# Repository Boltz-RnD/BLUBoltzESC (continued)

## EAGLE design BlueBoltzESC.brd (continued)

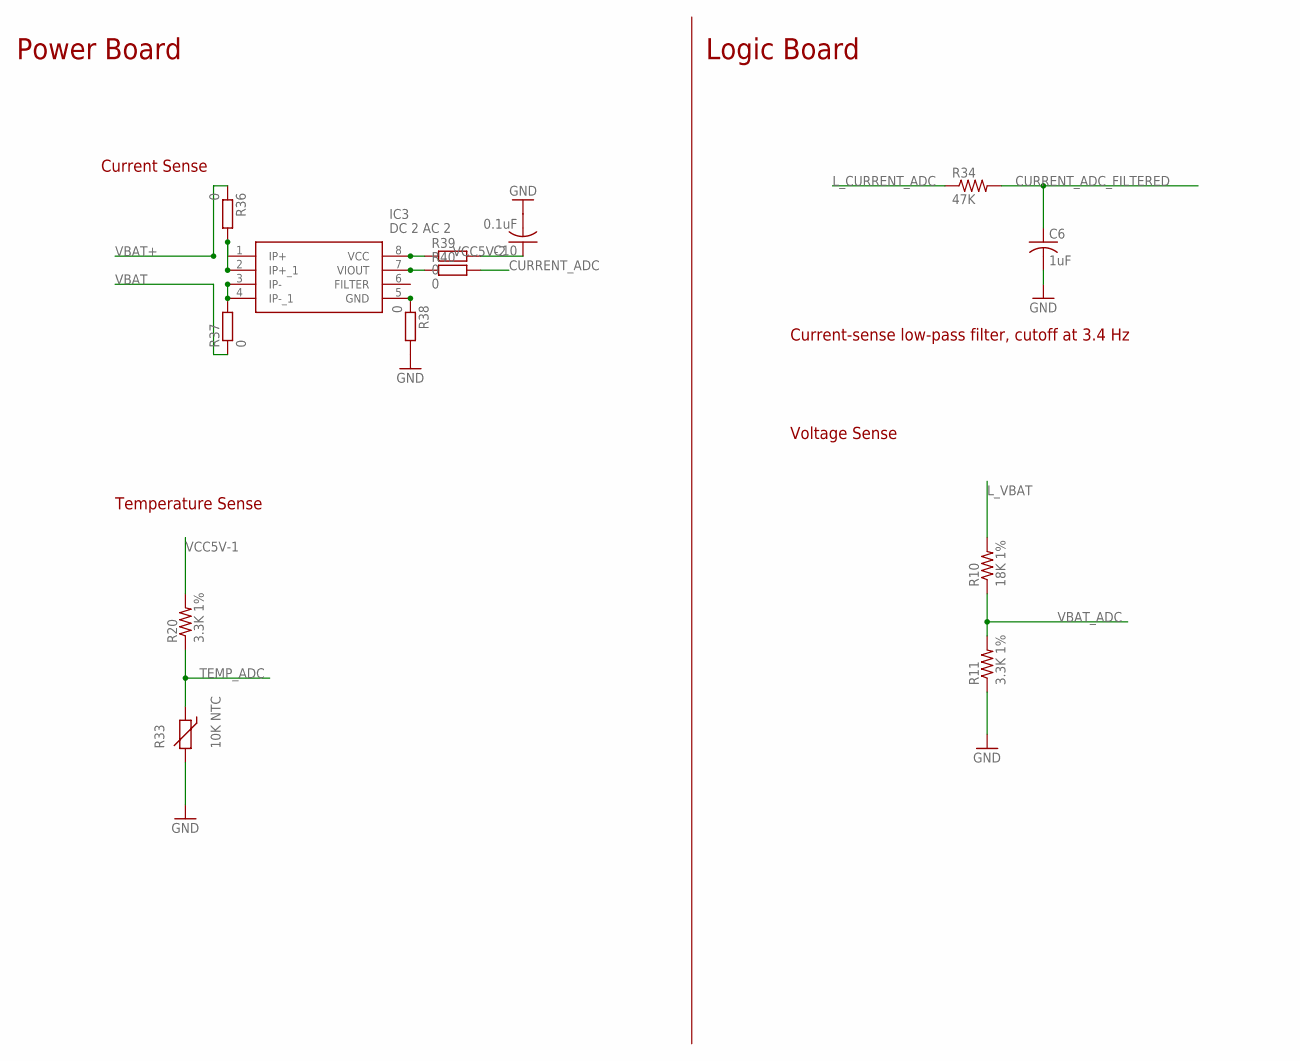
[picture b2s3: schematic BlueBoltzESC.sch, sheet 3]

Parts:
C6: 1uF; C025-030X050
C10: 0.1uF; C025-030X050
IC3: DC 2 AC 2; SOIC127P600X175-8N
R10: 18K 1%; 0207/10
R11, R20: 3.3K 1%; 0207/10
R33: 10K NTC; R-5
R34: 47K; 0207/10
R36, R37, R38, R39, R40: 0; MINI_MELF-0102R

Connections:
CURRENT_ADC: R40.2; also elsewhere on the board
CURRENT_ADC_FILTERED: C6.1, R34.2; also elsewhere on the board
GND: C10.2, R33.2, R38.2; also elsewhere on the board
L_CURRENT_ADC: R34.1; also elsewhere on the board
L_GND: C6.2, R11.1; also elsewhere on the board
L_VBAT: R10.2; also elsewhere on the board
unnamed: IC3.1 (IP+), IC3.2 (IP+_1), R36.2
unnamed: IC3.3 (IP-), IC3.4 (IP-_1), R37.2
unnamed: IC3.5 (GND), R38.1
unnamed: IC3.8 (VCC), R39.1
unnamed: IC3.7 (VIOUT), R40.1
TEMP_ADC: R20.1, R33.1; also elsewhere on the board
VBAT: R37.1; also elsewhere on the board
VBAT+: R36.1; also elsewhere on the board
VBAT_ADC: R10.1, R11.2; also elsewhere on the board
VCC5V-1: R20.2; also elsewhere on the board
VCC5V-2: C10.1, R39.2; also elsewhere on the board

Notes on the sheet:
Power Board
Logic Board
Current-sense low-pass filter, cutoff at 3.4 Hz
Voltage Sense
Current Sense
Temperature Sense

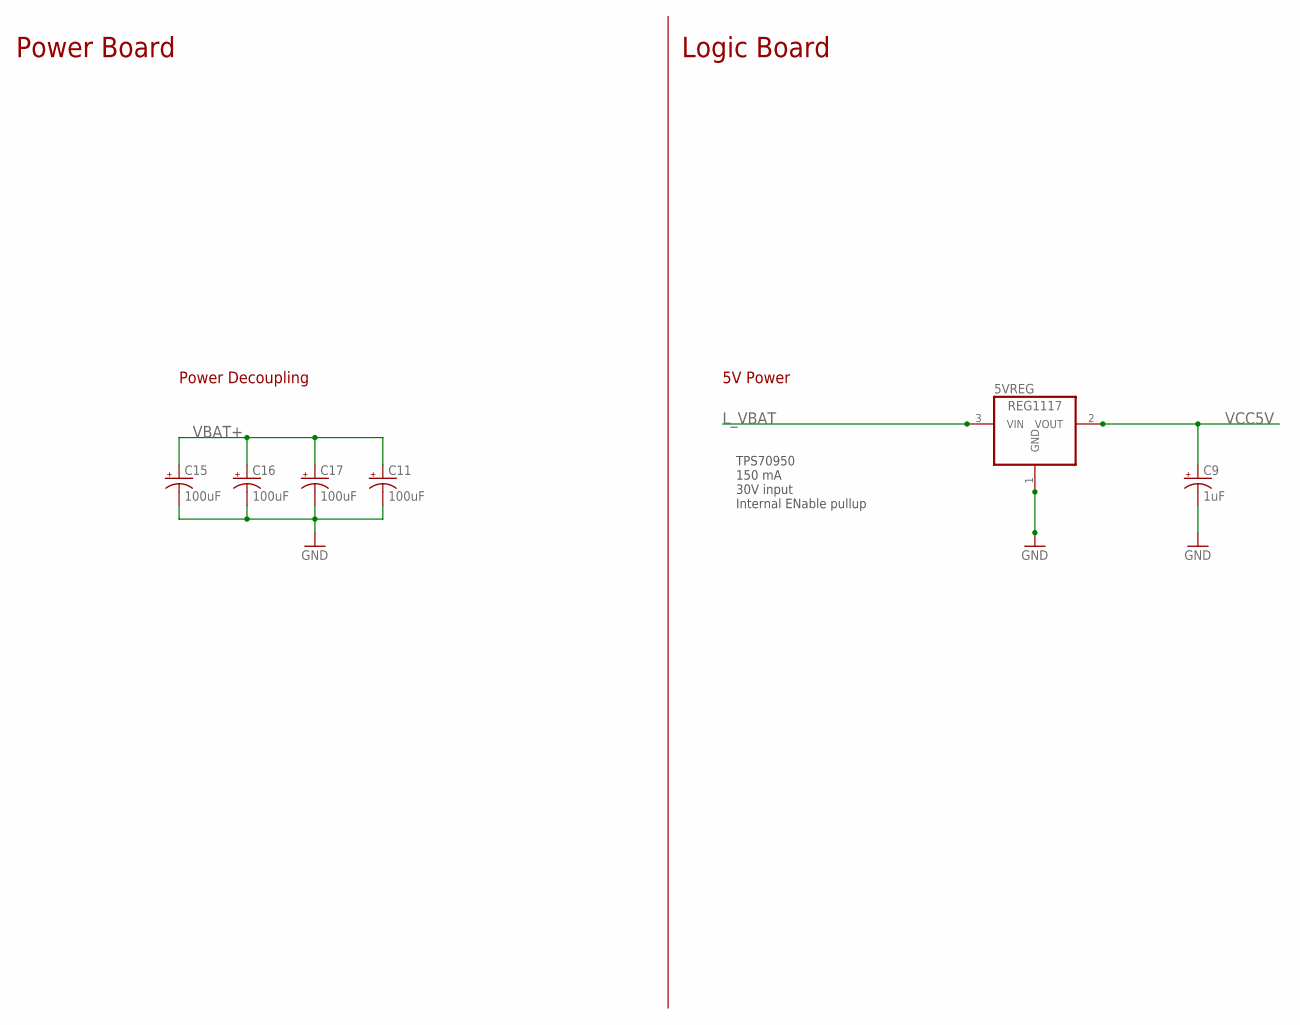
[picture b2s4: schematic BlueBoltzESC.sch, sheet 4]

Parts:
5VREG: REG1117; SOT223
C9: 1uF; E2,5-7
C11, C15, C16, C17: 100uF; E3,5-8

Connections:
GND: C11.-, C15.-, C16.-, C17.-; also elsewhere on the board
L_GND: 5VREG.1 (GND), C9.-; also elsewhere on the board
L_VBAT: 5VREG.3 (VIN); also elsewhere on the board
VBAT+: C11.+, C15.+, C16.+, C17.+; also elsewhere on the board
VCC5V: 5VREG.2 (VOUT), C9.+; also elsewhere on the board

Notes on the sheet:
Power Board
Logic Board
Power Decoupling
5V Power
TPS70950 150 mA 30V input Internal ENable pullup

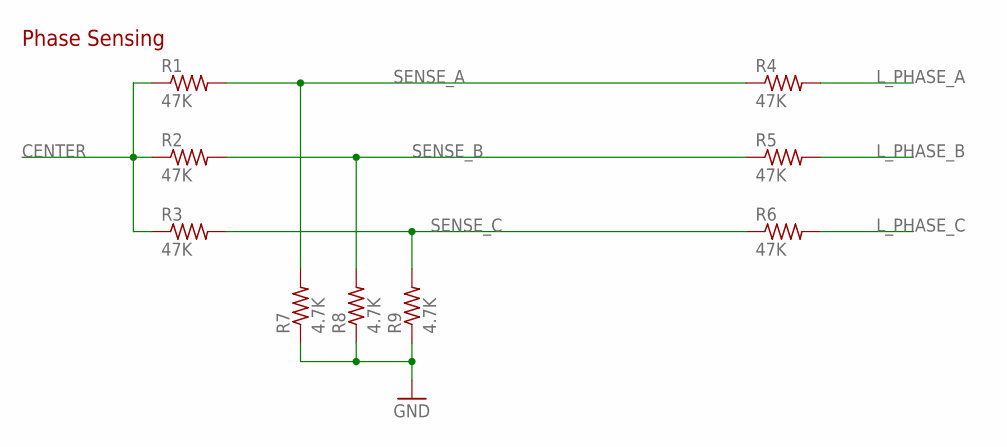
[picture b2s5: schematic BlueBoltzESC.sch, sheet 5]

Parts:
R1, R2, R3, R4, R5, R6: 47K; 0207/10
R7, R8, R9: 4.7K; 0207/10

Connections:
CENTER: R1.1, R2.1, R3.1; also elsewhere on the board
L_GND: R7.1, R8.1, R9.1; also elsewhere on the board
L_PHASE_A: R4.2; also elsewhere on the board
L_PHASE_B: R5.2; also elsewhere on the board
L_PHASE_C: R6.2; also elsewhere on the board
SENSE_A: R1.2, R4.1, R7.2; also elsewhere on the board
SENSE_B: R2.2, R5.1, R8.2; also elsewhere on the board
SENSE_C: R3.2, R6.1, R9.2; also elsewhere on the board

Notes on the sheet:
Phase Sensing

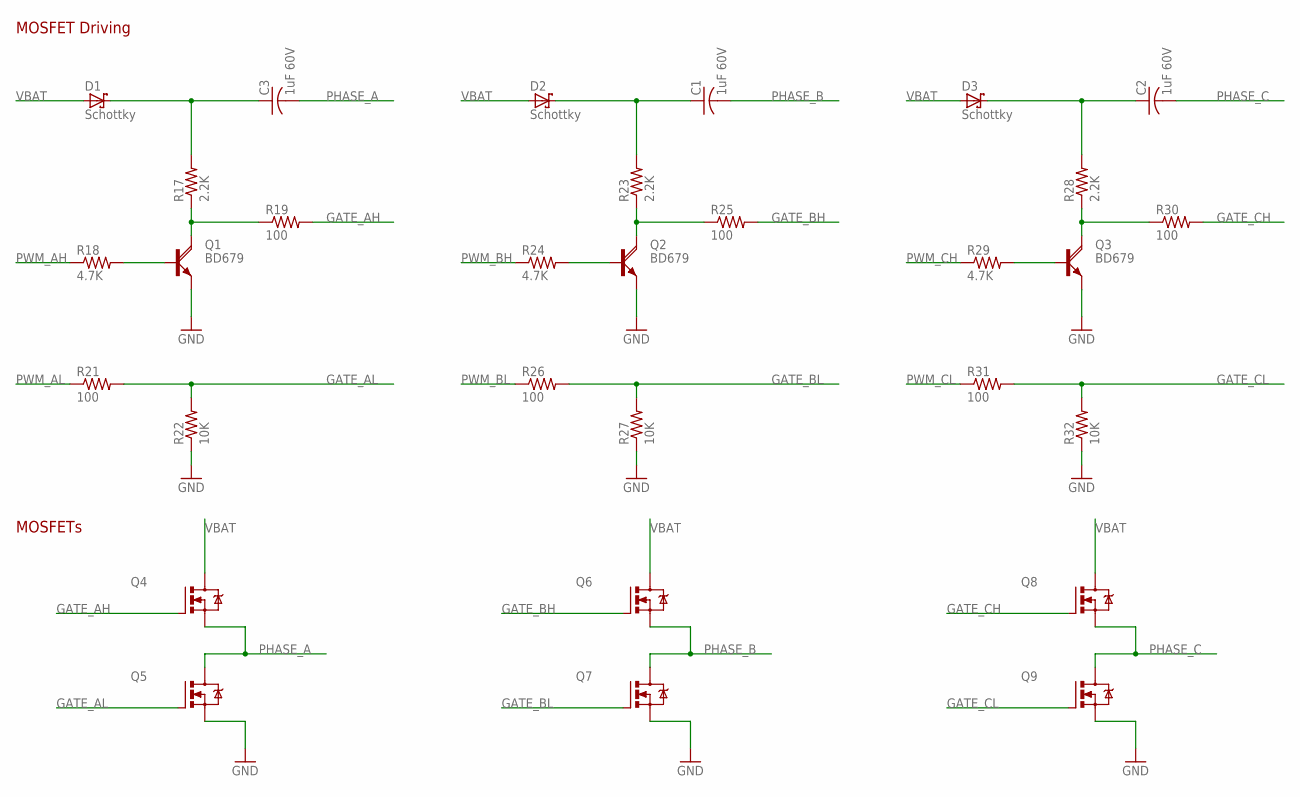
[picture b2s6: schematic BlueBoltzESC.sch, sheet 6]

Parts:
C1, C2, C3: 1uF 60V; C025-040X050
D1, D2, D3: Schottky; DO35-7
Q1, Q2, Q3: BD679; TO126AV
Q4, Q5, Q6, Q7, Q8, Q9: IRLZ44Z; TO220BH
R17, R23, R28: 2.2K; 0207/10
R18, R24, R29: 4.7K; 0207/10
R19, R21, R25, R26, R30, R31: 100; M3216
R22, R27, R32: 10K; M3216

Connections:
GATE_AH: Q4.G, R19.2
GATE_AL: Q5.G, R21.2, R22.2
GATE_BH: Q6.G, R25.2
GATE_BL: Q7.G, R26.2, R27.2
GATE_CH: Q8.G, R30.2
GATE_CL: Q9.G, R31.2, R32.2
GND: Q1.E, Q2.E, Q3.E, Q5.S, Q7.S, Q9.S, R22.1, R27.1, R32.1; also elsewhere on the board
unnamed: Q1.B, R18.2
unnamed: Q1.C, R17.1, R19.1
unnamed: Q2.B, R24.2
unnamed: Q2.C, R23.1, R25.1
unnamed: Q3.B, R29.2
unnamed: Q3.C, R28.1, R30.1
unnamed: C3.1, D1.C, R17.2
unnamed: C1.1, D2.C, R23.2
unnamed: C2.1, D3.C, R28.2
PHASE_A: C3.2, Q4.S, Q5.D; also elsewhere on the board
PHASE_B: C1.2, Q6.S, Q7.D; also elsewhere on the board
PHASE_C: C2.2, Q8.S, Q9.D; also elsewhere on the board
PWM_AH: R18.1; also elsewhere on the board
PWM_AL: R21.1; also elsewhere on the board
PWM_BH: R24.1; also elsewhere on the board
PWM_BL: R26.1; also elsewhere on the board
PWM_CH: R29.1; also elsewhere on the board
PWM_CL: R31.1; also elsewhere on the board
VBAT: D1.A, D2.A, D3.A, Q4.D, Q6.D, Q8.D; also elsewhere on the board

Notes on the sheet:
MOSFETs
MOSFET Driving

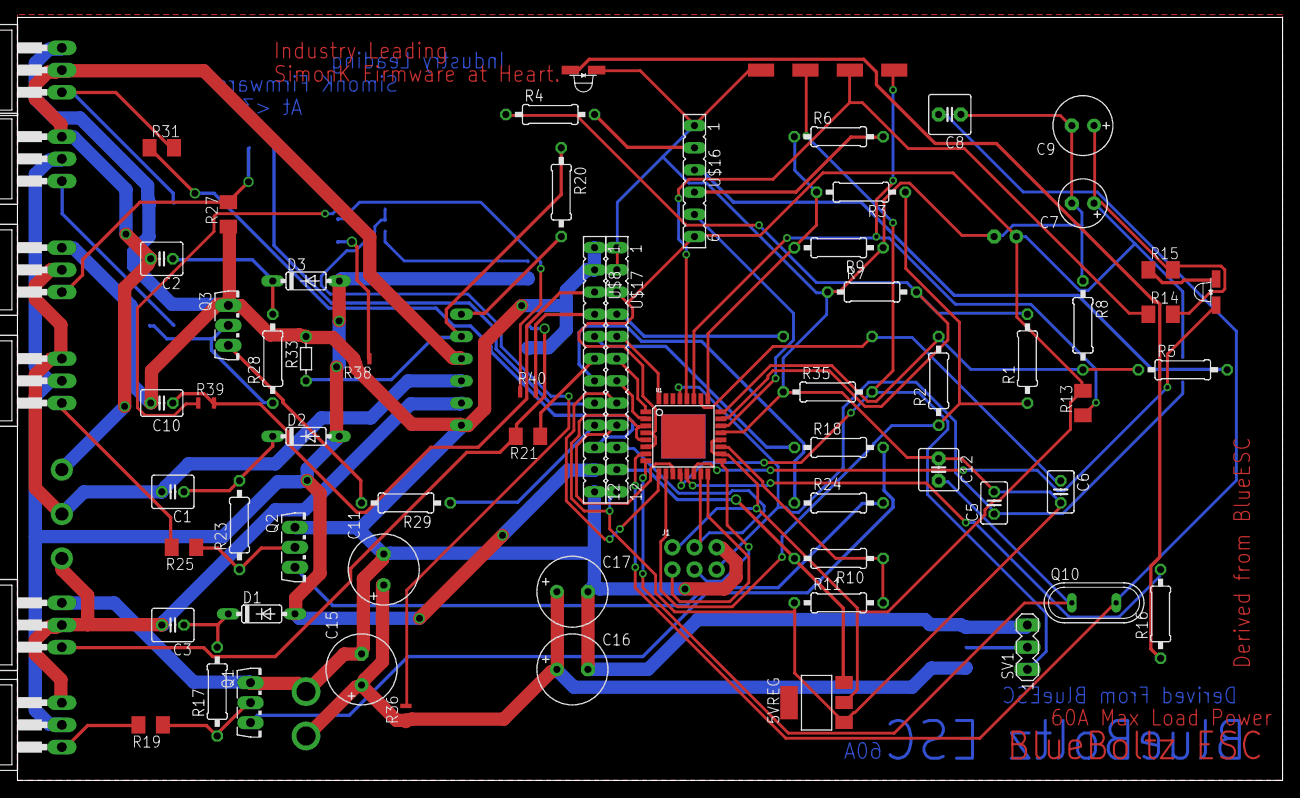
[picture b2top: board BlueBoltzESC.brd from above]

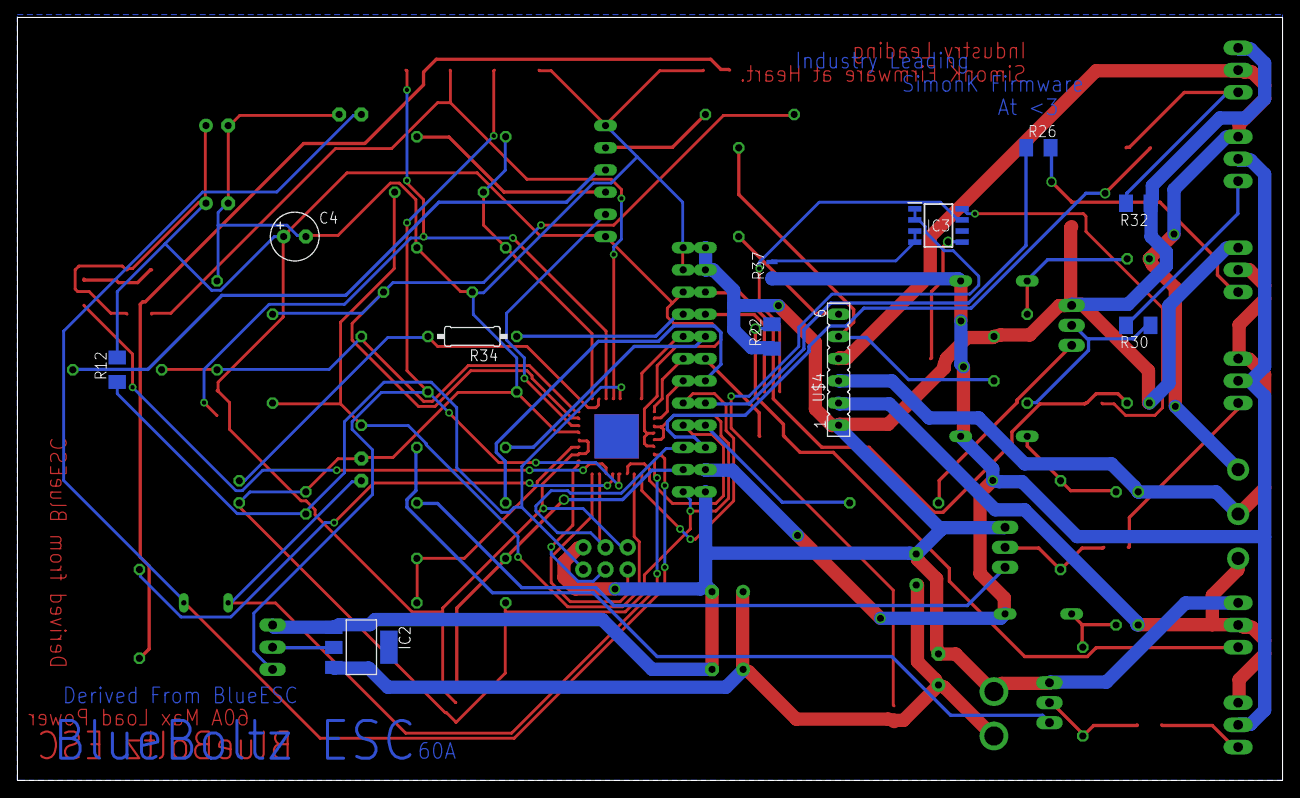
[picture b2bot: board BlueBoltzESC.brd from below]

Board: 2 copper layers, 144.8 x 87.3 mm, 89 parts (12 on the bottom side), 69 nets.

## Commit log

2018-03-15 Added Files
2018-03-31 Version 1.1 For BlueBoltzESC Board
    In this Version, The board is updated with a single board footprint, which minimizes hassles...
2018-03-31 PDF Deleted
2018-05-23 Improved the board
    Replaced IRFZ44n with IRLB4132
    Used more Easily Source-able SMD Components
2018-05-23 Update ReadME
    Updated new name for the board
2018-05-23 Updated Files
2018-05-23 Updated Power Lines
    Updated Power Lines with Thicker Rails
2018-05-23 Rearranged Files and Added Firmware Files
    Added Firmware and Rearranges files into thier respective folders.
2018-05-23 Fixed Dimension
2018-05-28 added schematics pdf
